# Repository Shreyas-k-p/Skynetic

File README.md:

# Skynetic
This project gives robots a sense of touch — distinguishing between gentle interaction and forceful impact using flex and pressure sensors. Built with ESP32, this is where code meets instinct.”

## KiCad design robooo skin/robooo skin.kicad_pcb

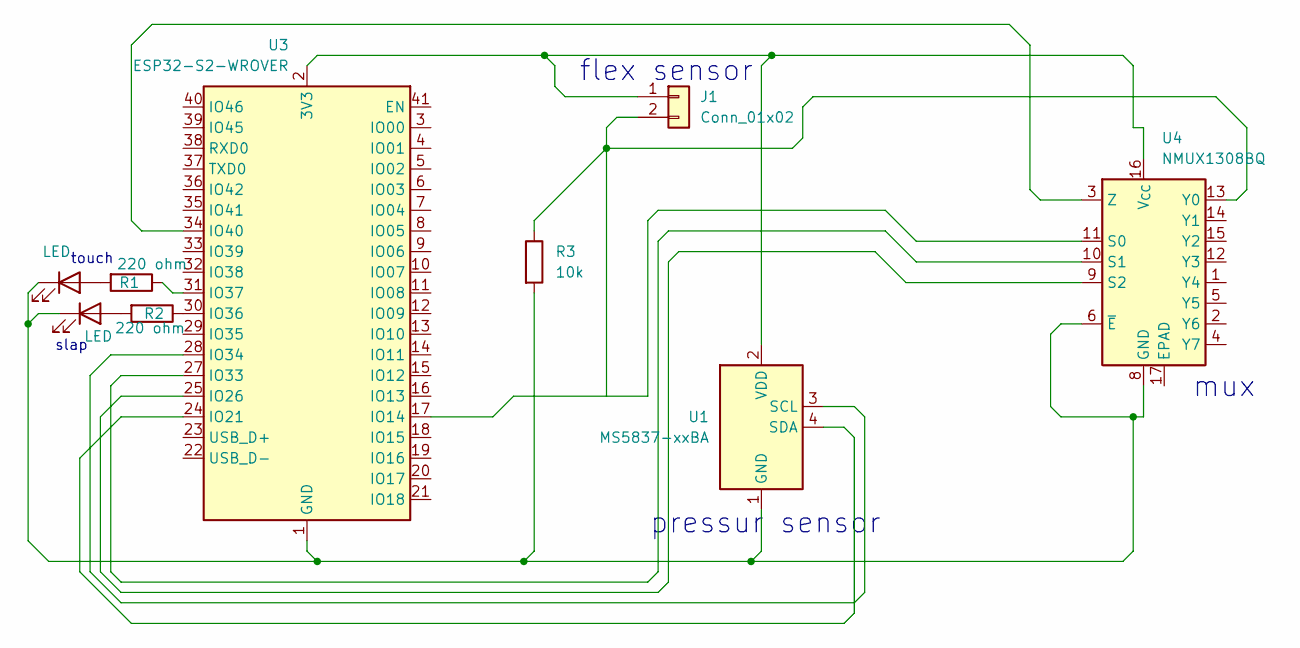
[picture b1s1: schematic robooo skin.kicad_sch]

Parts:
D1, D4: LED; LED_0402_1005Metric
J1: Conn_01x02; PinHeader_1x02_P1.00mm_Vertical
R1, R2: 220 ohm; R_0402_1005Metric
R3: 10k; R_0402_1005Metric
U1: MS5837-xxBA; TE_MS5837-xxBA
U3: ESP32-S2-WROVER
U4: NMUX1308BQ; DHVQFN-16-1EP_2.5x3.5mm_P0.5mm_EP1x2mm

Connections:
unnamed: D1.2 (A), R1.2
unnamed: D1.1 (K), D4.1 (K), R3.2, U1.1 (GND), U3.1 (GND), U3.26 (GND), U3.42 (GND), U3.43 (GND), U4.6 (~E), U4.8 (GND)
unnamed: D4.2 (A), R2.2
unnamed: J1.1, U1.2 (VDD), U3.2 (3V3), U4.16 (V_{CC})
unnamed: J1.2, R3.1, U4.13 (Y0)
unnamed: U1.3 (SCL), U3.28 (IO34)
unnamed: U1.4 (SDA), U3.24 (IO21)
unnamed: U3.17 (IO14), U4.11 (S0)
unnamed: U3.25 (IO26), U4.9 (S2)
unnamed: U3.27 (IO33), U4.10 (S1)
unnamed: R2.1, U3.30 (IO36)
unnamed: R1.1, U3.31 (IO37)
unnamed: U3.34 (IO40), U4.3 (Z)

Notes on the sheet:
touch
slap
mux
pressur sensor
flex sensor

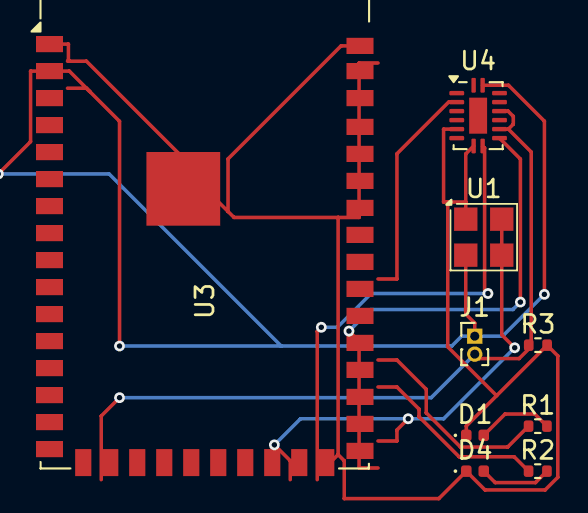
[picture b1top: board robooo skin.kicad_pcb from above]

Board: 2 copper layers, 9 parts (0 on the bottom side), 13 nets.

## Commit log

2025-06-28 circuit diagram screenshot for SKYNETIC project
    # 🤖 Sensei Skin: Robotic Touch & Slap Detection System
    ## 📜 Description
    A robotic skin system built using **ESP32-S2-WROVER**, **flex sensors**, and an **MS5837 pressure sensor**. The system detects whether a surface interaction is a gentle touch or a slap and lights up 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
    ---
    ## 🧠 Features
    - Detects **touch vs. slap** using combined sensor data
2025-06-28 code for touch and slap detection using flex and pressure sensors
    code for touch and slap detection using flex and pressure sensors
2025-06-28 Skynetic docs unlocked: Robots now feel emotions (and flex about it)
    ✨ Added complete documentation for Skynetic project
    Includes:
    - Introduction, advantages, applications, and conclusion
    - Project credits (Shreyas K P & Amrithraj, B.Tech 3rd Year ECE)
    - Quote capturing the emotion and vision of the project
    - Comparison table and simplified explanation for future references
2025-06-28 KiCad schematic and PCB design files for Skynetic
    - Added complete KiCad project files for Skynetic tactile sensing system
    - Includes schematic (.sch), PCB layout (.kicad_pcb), and symbol libraries
    - Represents connections for ESP32, flex sensor, pressure sensor, MUX, and LEDs
    - Will be used for future fabrication and prototyping
2025-06-28 block diagram for sensitive skin
    - Uploaded clear block diagram representing Skynetic's hardware architecture
    - Shows interaction between ESP32, flex sensor, pressure sensor, MUX, and LEDs
    - Useful for documentation, presentations, and future development reference
2025-06-28 Add files via upload
    - Uploaded clear block diagram representing Skynetic's hardware architecture
    - Shows interaction between ESP32, flex sensor, pressure sensor, MUX, and LEDs
    - Useful for documentation, presentations, and future development reference
2025-06-28 images
2025-06-29 Skynetic PPT initial version
    # 🤖 Sensei Skin: Robotic Touch & Slap Detection System
    ## 📜 Description
    A robotic skin system built using **ESP32-S2-WROVER**, **flex sensors**, and an **MS5837 pressure sensor**. The system detects whether a surface interaction is a gentle touch or a slap and lights up 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
    ---
    ## 🧠 Features
    - Detects **touch vs. slap** using combined sensor data
